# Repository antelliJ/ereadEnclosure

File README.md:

#ereader Enclosure
An expansion on [my ereader project](https://github.com/antelliJ/EPUB-Ereader) made using the arduino framework, and rendering using GxEPD2 on an ESP-32 S3

## Purpose
I found that my existing enclosure was just really bulky since it was all connected through jumper cables, and since I was using an old DVD player as the shell there was still lots of empty room. When I got my hands on a commercial ereader I realized that I could definitely make it smaller so it would be more comfortable to carry around

## Usage and info
Charging and data goes through a single usb c cable, an improvement frmo before where there was the port to charge, and 2 ports on the esp32 for jtag and usb. I guess those are still available, especially if you want jtag, you'd just need to remove the enclosure. But uploading and charging should be able to be done, this time also at the same time since it is using an MCP733871 which supports load sharing for powering the system and charging the battery

The schematic uses pin headers as placeholders for things like the switch and SPI sd card module, so ensure you choose what you need when designing it.

### File structure
`\PCB\` includes files relevant for the schematic, PCB design, and manufacturing. 
<br></br>
    `\PCB\production\` are the files used for PCB manufacturing

`\3dModel\` is intended for all 3d printed related files.
<br></br>
    `\3dModel\editable\` contains the editable files made in freecad for the enclosure

<br></br>
    `\3dModel\printable\` contains the print ready files as a `.3mf` file

`\Code\` Is a copy of the original repository. 
you can learn more about it [here](https://github.com/antelliJ/EPUB-Ereader)

It uses the GxEPD2 library to drive the display using SPI, using the arduino framework since that is what I am most comfortable with.

## Bill of Materials
A nicely formatted excel sheet is provided at `\PCB\production\ereader-bom.xlsx` with a few more comments. 
The below is just a static version of that...

| Designator | Footprint                                        | Quantity | Value                       | LCSC Part # | Alt Site                                                                                                       |
| ---------- | ------------------------------------------------ | -------- | --------------------------- | ----------- | -------------------------------------------------------------------------------------------------------------- |
| J1         | PinHeader_2x04_P2.54mm_Vertical                  | 1        | EPD-4.2in - 2x04            | C55829516   |                                                                                                                |
| J2         | Molex_PicoBlade_53047-0810_1x08_P1.25mm_Vertical | 1        | Remote Communication                      | C240845     |                                                                                                                |
| J3         | USB_C_Receptacle_GCT_USB4085                     | 1        | USB_C_Receptacle_USB2.0_14P | C2765186    |                                                                                                                |
| J4         | SPI-microsd-1x06                                 | 1        | SPI Micro SD card slot      |             | [https://www.aliexpress.com/item/1005008633757049.html](https://www.aliexpress.com/item/1005008633757049.html) |
| R1, R2     | 603                                              | 2        | 5.1k                        | C23186      |                                                                                                                |
| SW1        | PinHeader_1x03_P2.54mm_Horizontal                | 1        | SW_SPDT                     | FILLER      |                                                                                                                |
| U1         | ESP32-S3-DevKitC                                 | 1        | ESP32-S3-DevKitC            |             | https://www.aliexpress.com/item/1005007319706057.html                                                          |
| U2         | MCP73871                                         | 1        | MCP73871                    |             | https://www.aliexpress.com/item/32779467674.html                                                               |
| U3         | Buck Boost 3v3                                   | 1        | Buck Boost Converter        |             | https://www.aliexpress.com/item/1005006289357253.html                                                          |

A 10k thermistor is also used by the MCP73871 alongside a capacitor, which is usually given with the module.

## References
A lot of things were picked up on the way of creating this project spontaneously

used [Table to Markdown](https://tabletomarkdown.com/convert-spreadsheet-to-markdown/) to make the above BOM in the readme

There is some AI usage in the original E-reader project code, as follows:
- Code autocomplete and debugging
- AI explanations for unfamiliar C++ concepts
- Drafting PlatformIO calls for building

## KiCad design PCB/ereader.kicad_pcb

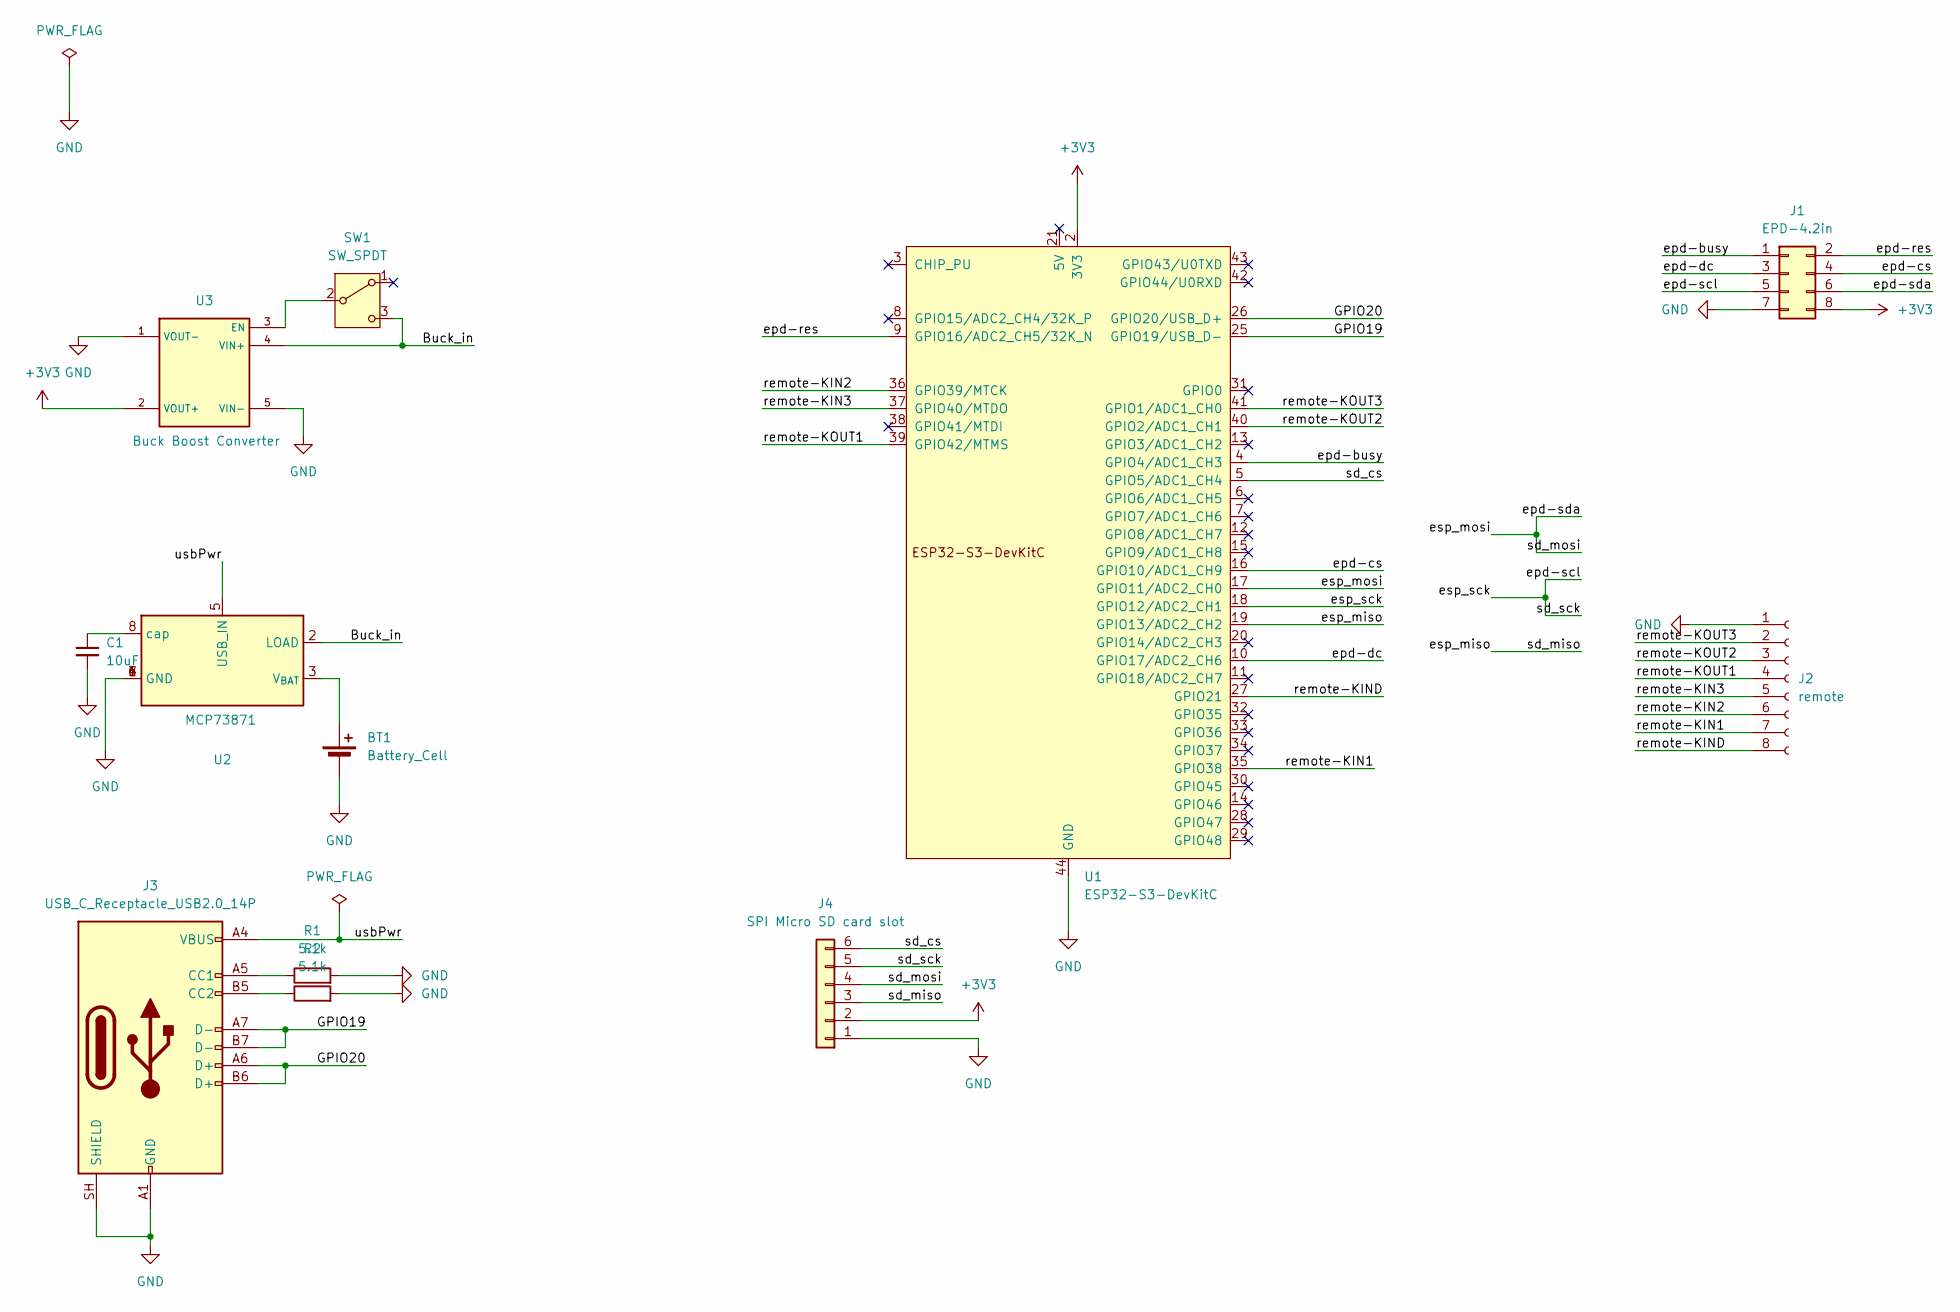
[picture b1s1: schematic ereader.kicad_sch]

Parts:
BT1: Battery_Cell; BatteryHolder_Lipo
C1: 10uF; C_0603_1608Metric_Pad1.08x0.95mm_HandSolder
J1: EPD-4.2in; PinHeader_2x04_P2.54mm_Vertical
J2: remote; Molex_PicoBlade_53047-0810_1x08_P1.25mm_Vertical
J3: USB_C_Receptacle_USB2.0_14P; USB_C_Receptacle_GCT_USB4085
J4: SPI Micro SD card slot; SPI-microsd-1x06
R1, R2: 5.1k; R_0603_1608Metric_Pad0.98x0.95mm_HandSolder
SW1: SW_SPDT; PinHeader_1x03_P2.54mm_Horizontal
U1: ESP32-S3-DevKitC
U2: MCP73871
U3: Buck Boost Converter; Buck Boost 3v3

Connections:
+3V3: J1.8, J4.2, U1.1 (3V3), U1.2 (3V3), U3.2 (VOUT+)
/Buck_in: SW1.3 (C), U2.2 (LOAD), U3.4 (VIN+)
/GPIO19: J3.A7 (D-), J3.B7 (D-), U1.25 (GPIO19/USB_D-)
/GPIO20: J3.A6 (D+), J3.B6 (D+), U1.26 (GPIO20/USB_D+)
/epd-busy: J1.1, U1.4 (GPIO4/ADC1_CH3)
/epd-cs: J1.4, U1.16 (GPIO10/ADC1_CH9)
/epd-dc: J1.3, U1.10 (GPIO17/ADC2_CH6)
/epd-res: J1.2, U1.9 (GPIO16/ADC2_CH5/32K_N)
/epd-scl: J1.5, J4.5, U1.18 (GPIO12/ADC2_CH1)
/epd-sda: J1.6, J4.4, U1.17 (GPIO11/ADC2_CH0)
/esp_miso: J4.3, U1.19 (GPIO13/ADC2_CH2)
/remote-KIN1: J2.7, U1.35 (GPIO38)
/remote-KIN2: J2.6, U1.36 (GPIO39/MTCK)
/remote-KIN3: J2.5, U1.37 (GPIO40/MTDO)
/remote-KIND: J2.8, U1.27 (GPIO21)
/remote-KOUT1: J2.4, U1.39 (GPIO42/MTMS)
/remote-KOUT2: J2.3, U1.40 (GPIO2/ADC1_CH1)
/remote-KOUT3: J2.2, U1.41 (GPIO1/ADC1_CH0)
/sd_cs: J4.6, U1.5 (GPIO5/ADC1_CH4)
/usbPwr: J3.A4 (VBUS), J3.A9 (VBUS), J3.B4 (VBUS), J3.B9 (VBUS), U2.5 (USB_IN)
GND: BT1.2 (-), C1.2, J1.7, J2.1, J3.A1 (GND), J3.A12 (GND), J3.B1 (GND), J3.B12 (GND), J3.SH (SHIELD), J4.1, R1.2, R2.2, U1.22 (GND), U1.23 (GND), U1.24 (GND), U1.44 (GND), U2.1 (GND), U2.4 (GND), U2.6 (GND), U2.7 (GND), U3.1 (VOUT-), U3.5 (VIN-)
unnamed: BT1.1 (+), U2.3 (V_{BAT})
unnamed: J3.A5 (CC1), R1.1
unnamed: J3.B5 (CC2), R2.1
unnamed: SW1.2 (B), U3.3 (EN)
unnamed: C1.1, U2.8 (cap)

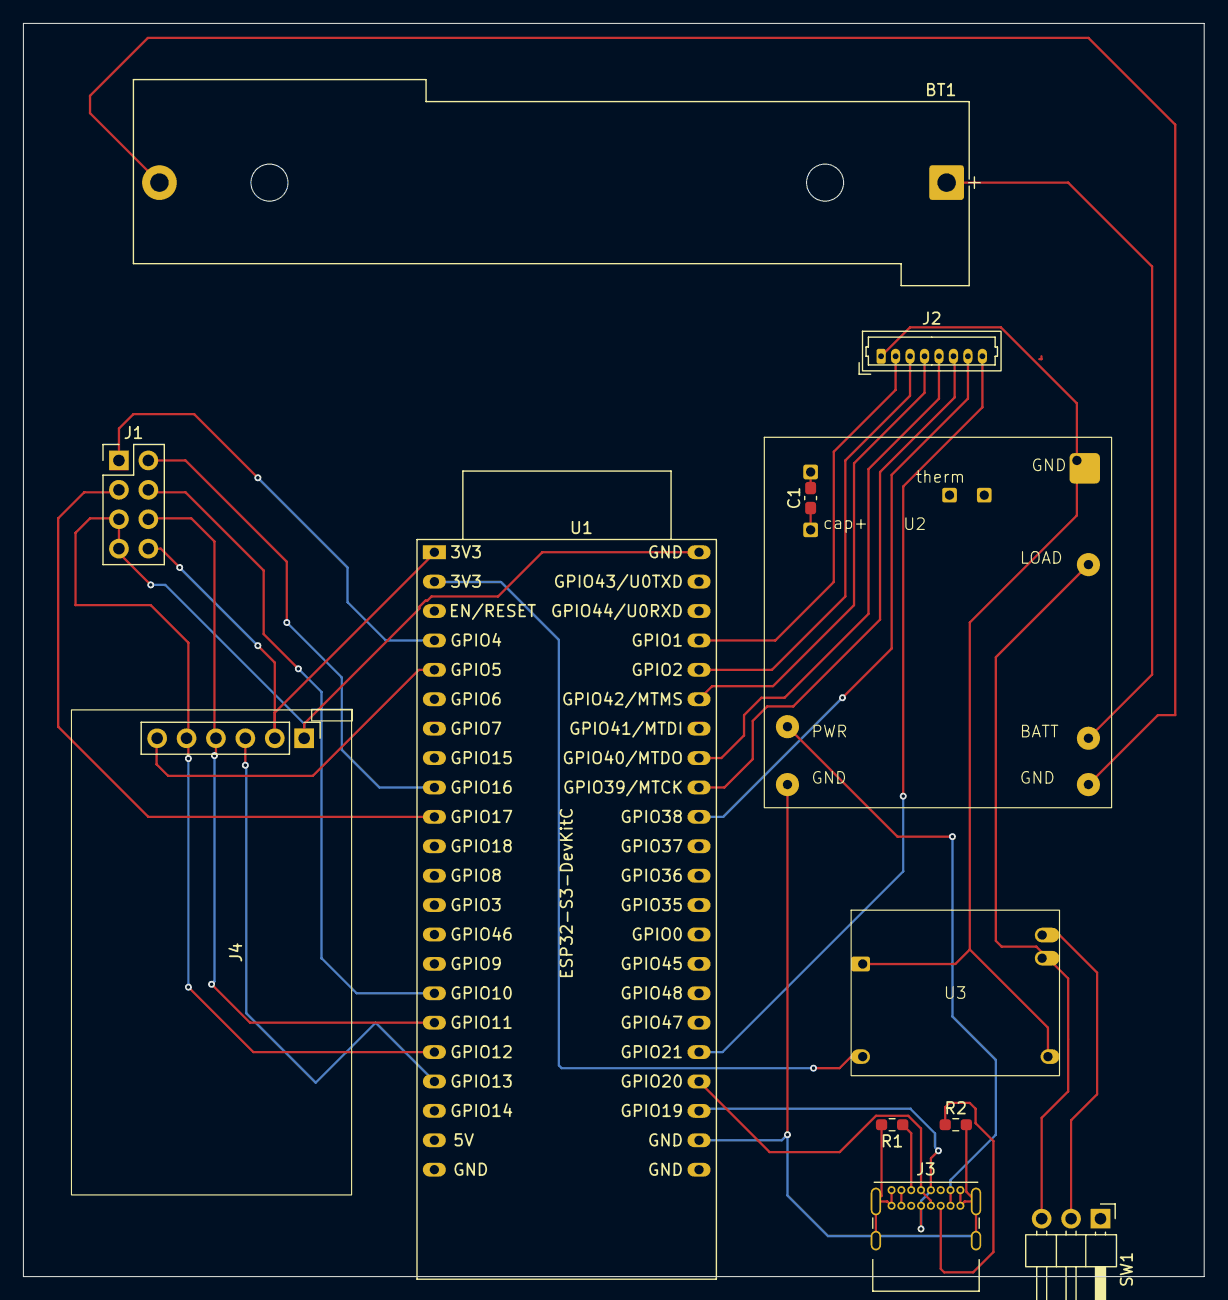
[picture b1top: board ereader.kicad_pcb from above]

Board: 2 copper layers, 102.0 x 108.2 mm, 12 parts (0 on the bottom side), 26 nets.

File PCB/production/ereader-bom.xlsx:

Designator | Footprint | Quantity | Value | LCSC Part # | Alt Site | Comments
BT1 | BatteryHolder_Lipo | 1 | Battery_Cell |  |  | I plan on just wiring it
C1 | 603 | 1 | 10uF | C15850 |  | Usually Provided, alongside a thermistor that wasn't on the schematic
J1 | PinHeader_2x04_P2.54mm_Vertical | 1 | EPD-4.2in - 2x04 | C55829516
J2 | Molex_PicoBlade_53047-0810_1x08_P1.25mm_Vertical | 1 | remote | C240845
J3 | USB_C_Receptacle_GCT_USB4085 | 1 | USB_C_Receptacle_USB2.0_14P | C2765186
J4 | SPI-microsd-1x06 | 1 | SPI Micro SD card slot |  | https://www.aliexpress.com/item/1005008633757049.html | many of these ali express products are clones so find whichever make sthe most 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
R1, R2 | 603 | 2 | 5.1k | C23186
SW1 | PinHeader_1x03_P2.54mm_Horizontal | 1 | SW_SPDT | FILLER |  | A standard thru hole switch, no header needed
U1 | ESP32-S3-DevKitC | 1 | ESP32-S3-DevKitC |  | https://www.aliexpress.com/item/1005007319706057.html | standard s3 devkit
U2 | MCP73871 | 1 | MCP73871 |  | https://www.aliexpress.com/item/32779467674.html
U3 | Buck Boost 3v3 | 1 | Buck Boost Converter |  | https://www.aliexpress.com/item/1005006289357253.html
